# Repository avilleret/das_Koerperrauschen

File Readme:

Repository for *das Körperrauschen* project dev

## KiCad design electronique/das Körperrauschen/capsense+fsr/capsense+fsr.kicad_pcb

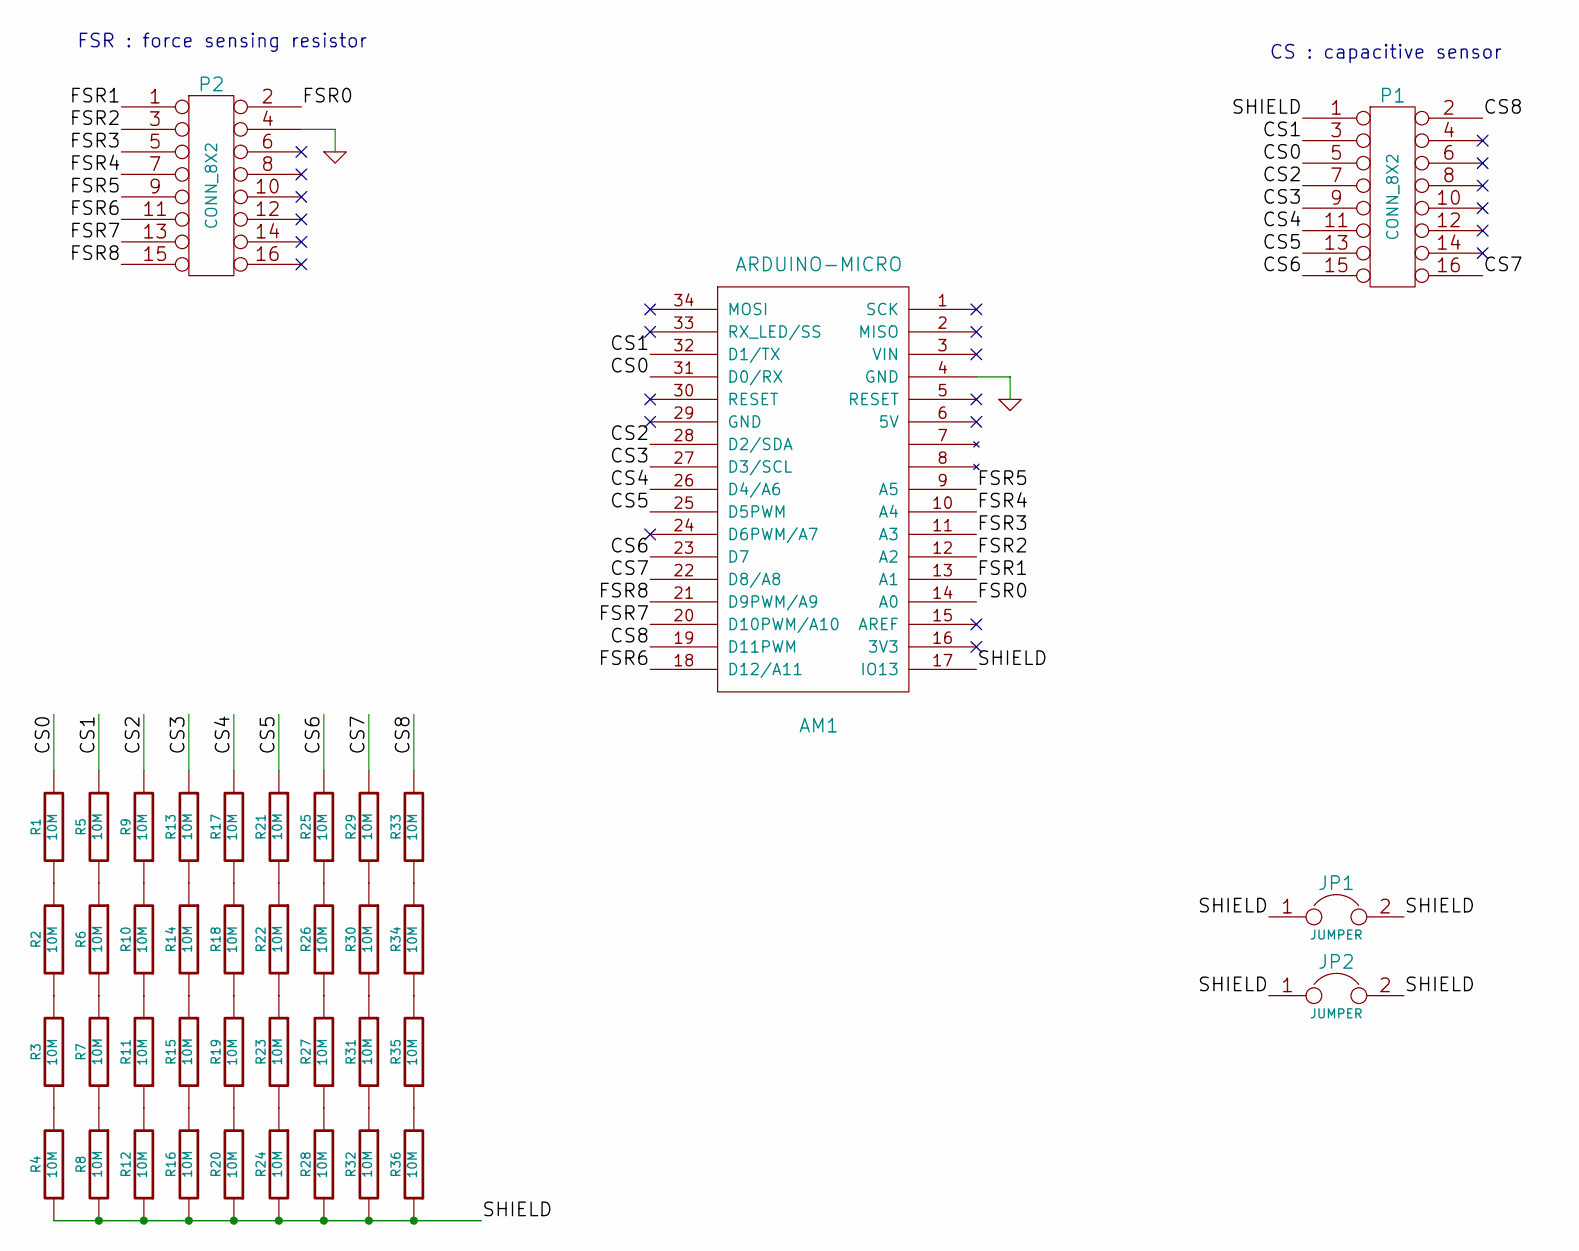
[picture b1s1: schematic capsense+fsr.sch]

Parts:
AM1: ARDUINO-MICRO
JP1, JP2: JUMPER
P1, P2: CONN_8X2
R1, R2, R3, R4, R5, R6, R7, R8, R9, R10, R11, R12, R13, R14, R15, R16, R17, R18, R19, R20, R21, R22, R23, R24, R25, R26, R27, R28, R29, R30, R31, R32, R33, R34, R35, R36: 10M

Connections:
/CS0: AM1.31 (D0/RX), P1.5, R1.2
/CS1: AM1.32 (D1/TX), P1.3, R5.1
/CS2: AM1.28 (D2/SDA), P1.7, R9.2
/CS3: AM1.27 (D3/SCL), P1.9, R13.1
/CS4: AM1.26 (D4/A6), P1.11, R17.2
/CS5: AM1.25 (D5PWM), P1.13, R21.1
/CS6: AM1.23 (D7), P1.15, R25.2
/CS7: AM1.22 (D8/A8), P1.16, R29.1
/CS8: AM1.19 (D11PWM), P1.2, R33.2
/FSR0: AM1.14 (A0), P2.2
/FSR1: AM1.13 (A1), P2.1
/FSR2: AM1.12 (A2), P2.3
/FSR3: AM1.11 (A3), P2.5
/FSR4: AM1.10 (A4), P2.7
/FSR5: AM1.9 (A5), P2.9
/FSR6: AM1.18 (D12/A11), P2.11
/FSR7: AM1.20 (D10PWM/A10), P2.13
/FSR8: AM1.21 (D9PWM/A9), P2.15
/SHIELD: AM1.17 (IO13), JP1.1, JP1.2, JP2.1, JP2.2, P1.1, R4.1, R8.2, R12.1, R16.2, R20.1, R24.2, R28.1, R32.2, R36.1
GND: AM1.4 (GND), P2.4
unnamed: R2.1, R3.2
unnamed: R3.1, R4.2
unnamed: R10.1, R11.2
unnamed: R9.1, R10.2
unnamed: R26.1, R27.2
unnamed: R25.1, R26.2
unnamed: R27.1, R28.2
unnamed: R21.2, R22.1
unnamed: R22.2, R23.1
unnamed: R23.2, R24.1
unnamed: R17.1, R18.2
unnamed: R18.1, R19.2
unnamed: R19.1, R20.2
unnamed: R13.2, R14.1
unnamed: R14.2, R15.1
unnamed: R15.2, R16.1
unnamed: R34.1, R35.2
unnamed: R1.1, R2.2
unnamed: R33.1, R34.2
unnamed: R11.1, R12.2
unnamed: R35.1, R36.2
unnamed: R29.2, R30.1
unnamed: R30.2, R31.1
unnamed: R31.2, R32.1
unnamed: R5.2, R6.1
unnamed: R6.2, R7.1
unnamed: R7.2, R8.1

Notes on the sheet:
CS : capacitive sensor
FSR : force sensing resistor

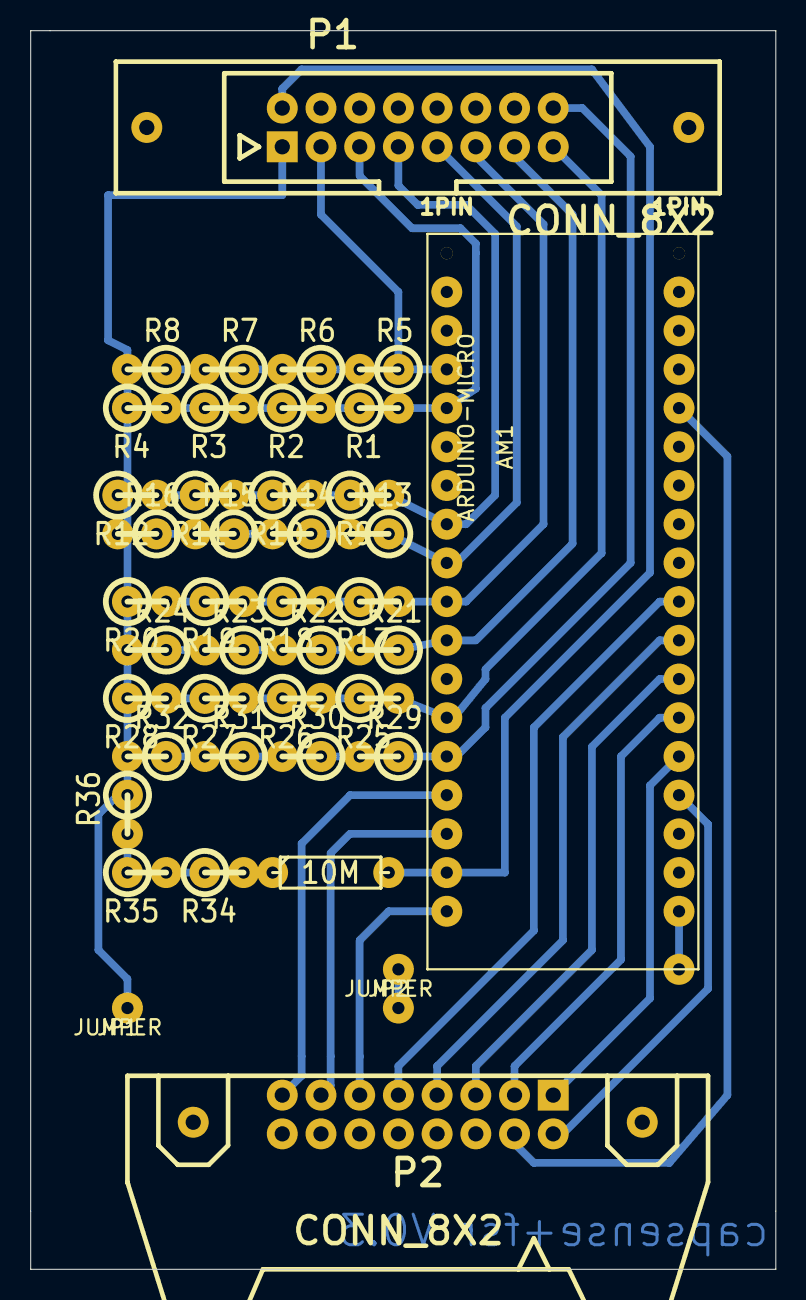
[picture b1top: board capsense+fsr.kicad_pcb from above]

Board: 2 copper layers, 48.9 x 81.3 mm, 43 parts (0 on the bottom side), 47 nets.

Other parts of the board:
1PIN, 1PIN#2: P***; 1pin

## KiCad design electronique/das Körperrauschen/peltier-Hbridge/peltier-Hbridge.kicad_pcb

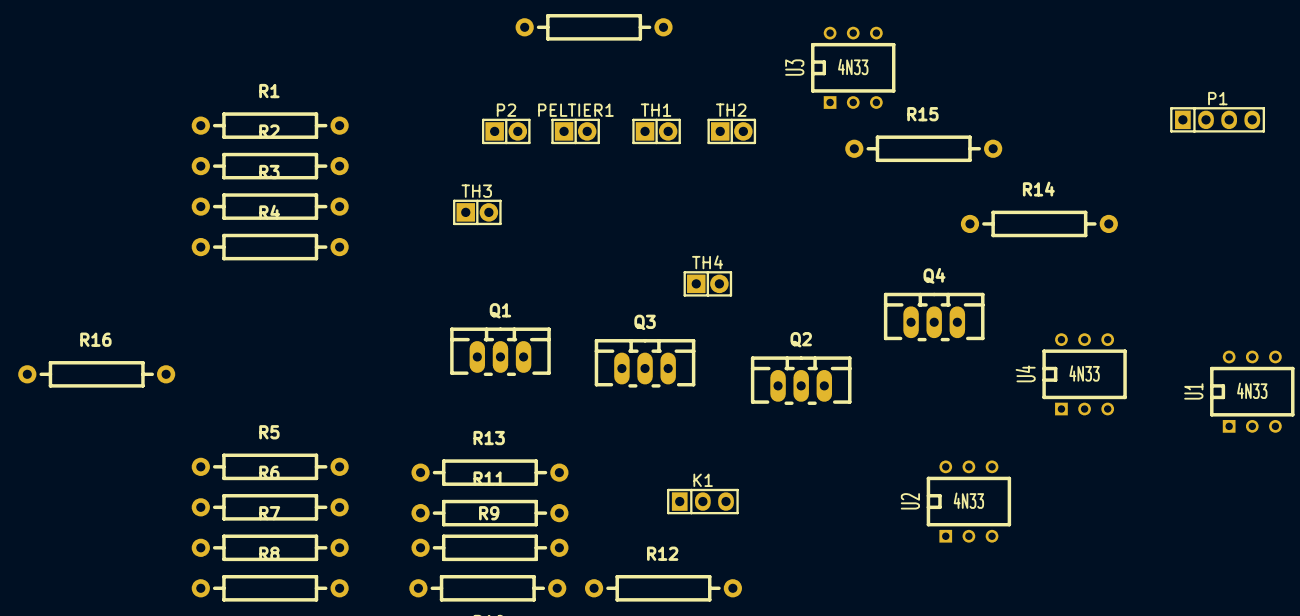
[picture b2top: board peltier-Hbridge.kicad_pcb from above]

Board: 2 copper layers, 33 parts (0 on the bottom side), 24 nets, no tracks yet.

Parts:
AM1: ARDUINO-MICRO; Resistor_Horizontal_RM15mm
K1: CONN_3; Pin_Header_Straight_1x03
P1: CONN_4; Pin_Header_Straight_1x04
P2: CONN_2; Pin_Header_Straight_1x02
PELTIER1: R; Pin_Header_Straight_1x02
Q1, Q3: MOSFET_P; TO-220_FET-GDS_Vertical_LargePads
Q2, Q4: MOSFET_N; TO-220_FET-GDS_Vertical_LargePads
R1, R2, R3, R4, R9, R10, R11, R12: 10k; Resistor_Horizontal_RM15mm
R5, R6, R15, R16: 470; Resistor_Horizontal_RM15mm
R7, R8, R13, R14: 1k; Resistor_Horizontal_RM15mm
TH1, TH2, TH3, TH4: THERMISTOR; Pin_Header_Straight_1x02
U1, U2, U3, U4: 4N33; DIP-6__300

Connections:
+12V: K1.2, P1.2, P2.2, Q1.S, Q3.S, R9.2, R11.2, U2.5, U4.5
/H-bridge Peltier Control/cool: R6.1, R16.1, U1.2
/H-bridge Peltier Control/ena*: U2.2, U4.2
/H-bridge Peltier Control/heat: R5.1, R15.1, U3.2
GND: K1.1, P1.1, P2.1, Q2.S, Q4.S, R10.1, R12.1, TH1.2, TH2.2, TH3.2, TH4.2, U1.4, U3.4
unnamed: R1.1, R2.1, R3.1, R4.1
unnamed: R4.2, TH4.1
unnamed: R3.2, TH3.1
unnamed: R2.2, TH2.1
unnamed: R1.2, TH1.1
unnamed: PELTIER1.1, Q1.D, Q2.D
unnamed: PELTIER1.2, Q3.D, Q4.D
unnamed: Q1.G, R7.2, R9.1
unnamed: Q2.G, R8.2, R10.2
unnamed: Q3.G, R11.1, R13.1
unnamed: Q4.G, R12.2, R14.1
unnamed: R5.2, U1.1
unnamed: R6.2, U2.1
unnamed: R7.1, U1.5
unnamed: R8.1, U2.4
unnamed: R13.2, U3.5
unnamed: R14.2, U4.4
unnamed: R15.2, U4.1
unnamed: R16.2, U3.1

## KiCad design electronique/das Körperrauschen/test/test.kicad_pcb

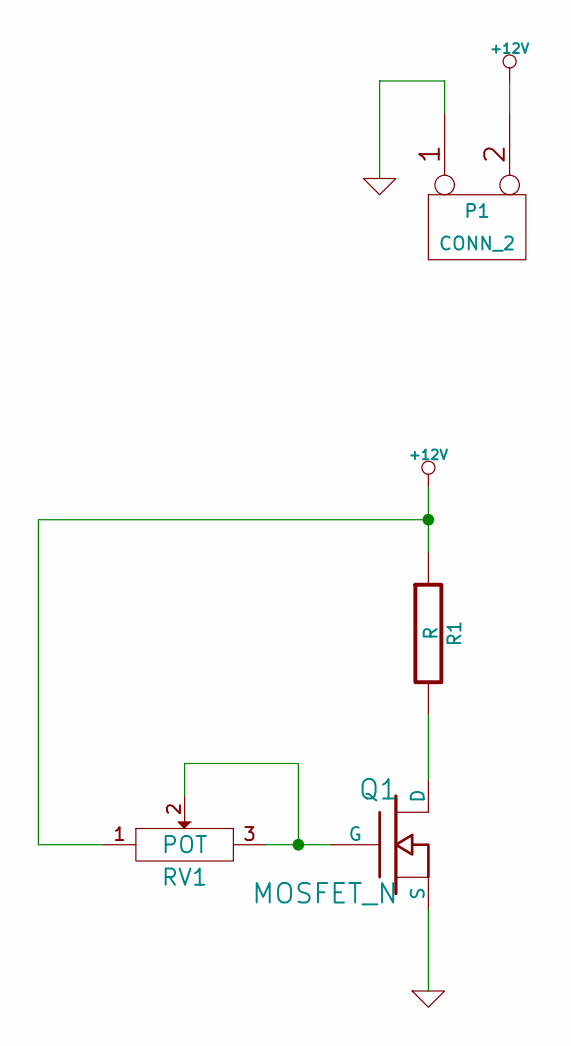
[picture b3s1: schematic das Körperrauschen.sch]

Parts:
P1: CONN_2
Q1: MOSFET_N
R1: R
RV1: POT

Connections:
+12V: P1.2 (PM), R1.1, RV1.1
GND: P1.1, Q1.S
unnamed: Q1.D, R1.2
unnamed: Q1.G, RV1.2, RV1.3

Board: 2 copper layers, 4 parts (0 on the bottom side), 4 nets, no tracks yet.

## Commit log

2014-02-09 add .gitignore
2014-02-09 update . gitignore
2014-02-09 address_setup project
2014-02-09 *capsense+fsr* project first commit
2014-02-09 first commit of pd patches
2014-02-20 more verbose script
2014-02-20 improve scanning and OSC communication
2014-02-20 update patches and add some abstractions
2014-02-20 rename source file
2014-02-21 put all parameters in a strut{} and save it to EEPROM
2014-02-21 restart sketch if serial connection is close
2014-02-21 update patches
2014-02-21 fix recall of timeout
2014-02-21 update patch
2014-02-22 optimize loop speed
    send as few OSC messsages as possible
    don't check Serial all
2014-02-22 update routeOSC binary
    fix a crash when wrong data are received
2014-02-22 desactivate autocal and put the garde fou in the right place
2014-02-22 speed up loop
    scan all CS in each loop (works with very low sensibility i.e. 2)
    loop duration : 13 ~ 20 ms depending on the environment
    clip sensibility param
2014-02-23 CS report -2 when timeout occurs
2014-02-23 update patches
    Main_sensor-processing : process all sensors values and send them over network
    Main_display : show all sensor data after processing
    oscilloscope are now made with translate and double gemvertexbuffer
2014-02-23 update cs_filter
    - make a simple but stable DC remover
    - delete all Gem objects in Main_sensor-processing.pd
2014-02-23 update pd-patches
    add Maind_dsp.pd : the main patch for audio
    it's based on the sensor map made in Main_display.pd
    also update display : CS in red, FSR in green, red+green = yellow
2014-07-25 electronic project
2014-07-25 update Pd project
2014-07-25 add puremapping to git
2014-11-01 fix typo, add comments / documentation
2014-11-01 fix typo
2014-11-01 return -1 for disabled sensors
2014-11-01 update Pd patches
2014-11-01 remove unused loopDelay parameter
2014-11-02 label color changes according to sensor status
    red : timeout (-2)
    green : ok
    gray : disabled (-1)
2014-11-22 don't override parameters
2014-11-22 update patchs
2014-11-22 add abstraction rather than just a link
2014-11-30 increase reconnection delay
    TODO : delay reconnection after board detection
2014-11-30 add x86_64 binaries
2015-01-02 move externals to pd-externals folder
2015-01-02 two USB DMX interface test
2015-01-02 remobe lib folder, use a global one instead
2015-01-02 coordinates update
2015-01-02 update vertexbuffer on redraw only
2015-01-02 another oscilloscope implementation
    this is less efficient than vertexbuffer version
2015-01-02 two synth
2015-01-02 update searching path and some other stuff
2015-01-02 deals with new USB DMX interface
2015-01-02 minor changes
2015-01-03 update FSR coordinates for board 3
2015-01-03 update sensor position
2015-01-03 remove old patch
2015-01-03 improve viewer
2015-01-03 change window offset
2015-01-06 remove unneeded files, add some new
2015-01-06 add shaders
2015-01-06 add new externals
2015-01-06 remove old binaries (replace by pd-externals folder)
2015-01-06 remove av externals (now in pd-externals fodler)
2015-01-18 update osc library to SVN rev17405
2015-01-18 use stream_check to open comport control
2015-01-18 add multichannel compressor
2015-01-18 add nusmuk-utils (for [once])
2015-01-18 add startup script
2015-01-18 add sound folder and ignore its content
2015-01-21 first day
2015-01-21 save
